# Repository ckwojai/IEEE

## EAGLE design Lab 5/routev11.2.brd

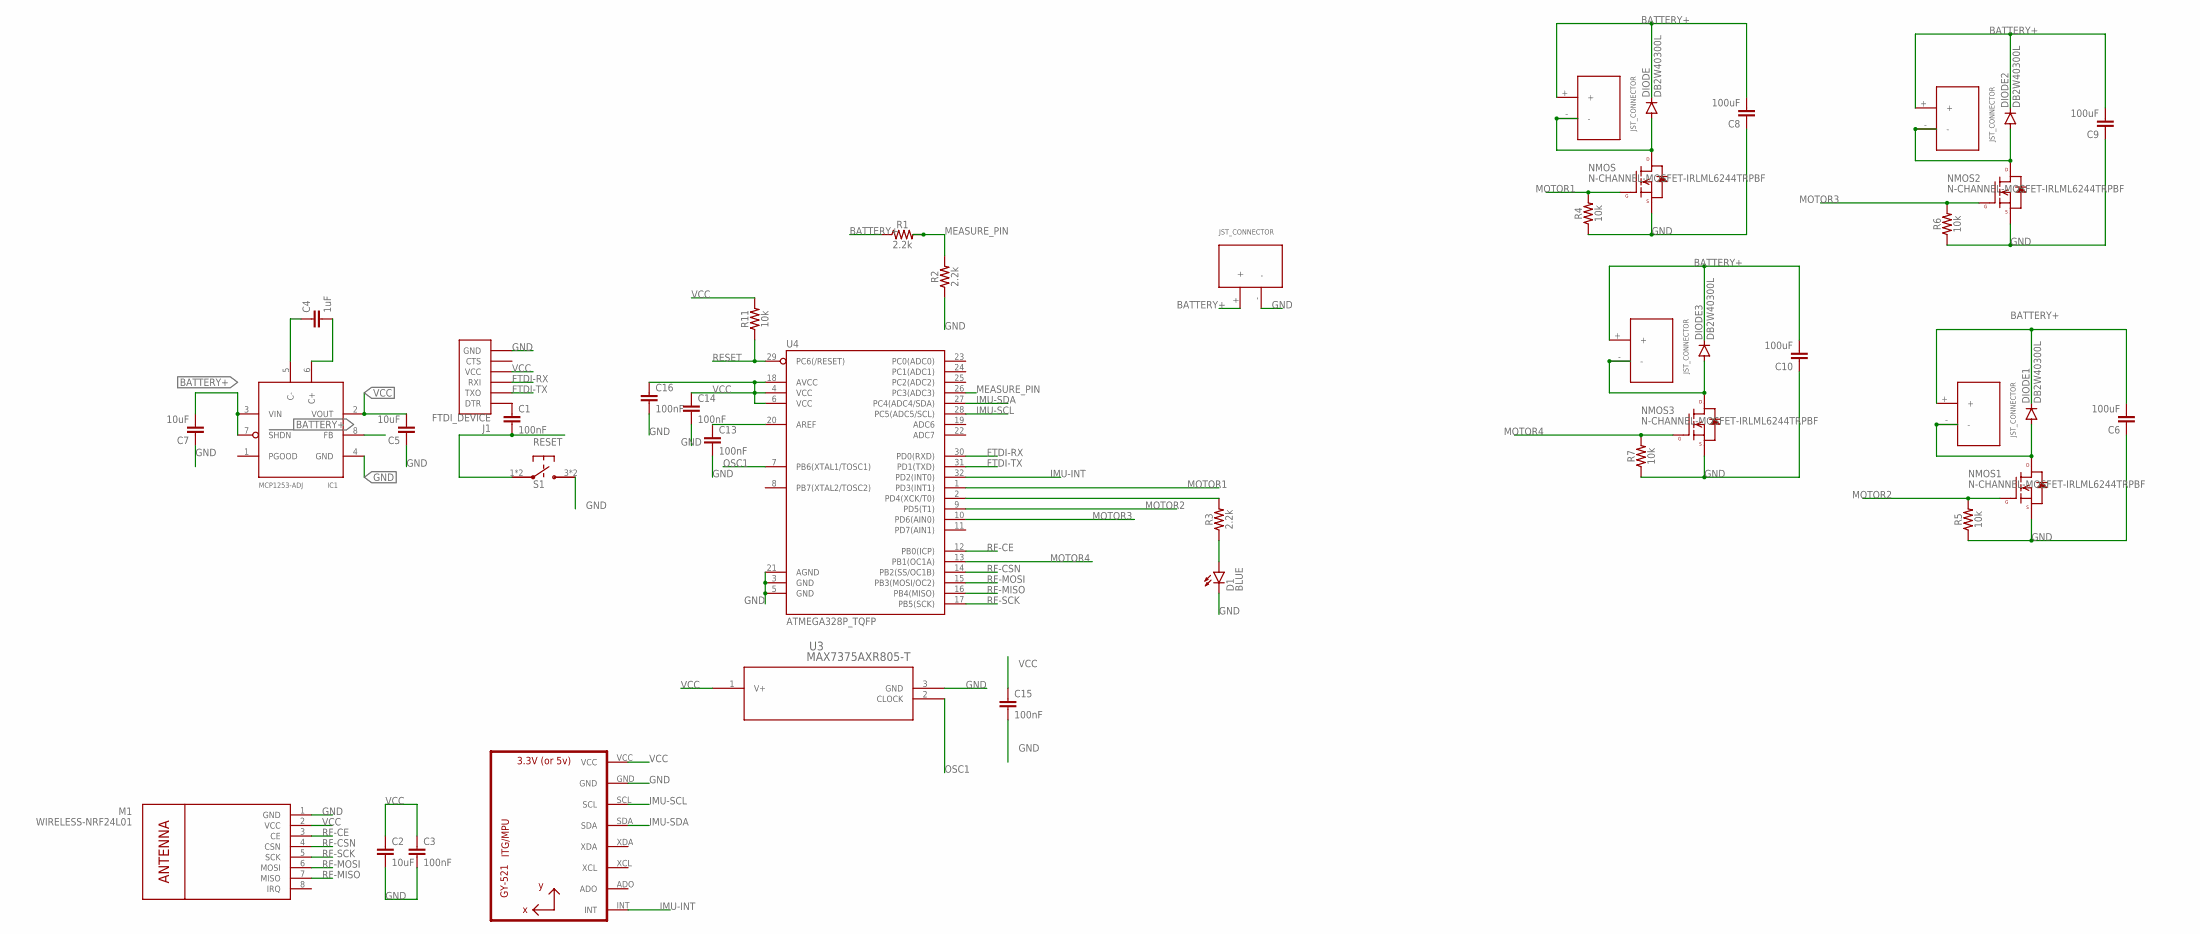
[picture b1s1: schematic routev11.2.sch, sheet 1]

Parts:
C1, C3, C13, C14, C15, C16: 100nF; 0603-CAP
C2, C5, C7: 10uF; 0603-CAP
C4: 1uF; 0603-CAP
C6, C8, C9, C10: 100uF; 1206
D1: BLUE; LED-0603
DIODE, DIODE1, DIODE2, DIODE3: DB2W40300L; MINI2-F3-B
IC1: MCP1253-ADJ; MSOP8
J1: FTDI_DEVICE; FTDI_DEVICE_SIDE
M1: WIRELESS-NRF24L01
MOTOR1, MOTOR2, MOTOR3, MOTOR4: JST_CONNECTOR_FEMALE
NMOS, NMOS1, NMOS2, NMOS3: N-CHANNEL-MOSFET-IRLML6244TRPBF; SOT23-3
R1, R2, R3: 2.2k; 0603
R4, R5, R6, R7, R11: 10k; 0603
S1: TL3315NF100Q
U2: GY-521MPU6050; GY-521
U3: MAX7375AXR805-T; 21-0075D
U4: ATMEGA328P_TQFP; TQFP32-08
U$1: JST_CONNECTOR_FEMALE

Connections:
BATTERY+: C6.2, C7.2, C8.2, C9.2, C10.2, DIODE.NEG (GPIN), DIODE1.NEG (GPIN), DIODE2.NEG (GPIN), DIODE3.NEG (GPIN), IC1.3 (VIN), IC1.7 (SHDN), IC1.8 (FB), MOTOR1.+, MOTOR2.+, MOTOR3.+, MOTOR4.+, R1.1, U$1.+
FTDI-RX: J1.P$3 (RXI), U4.30 (PD0(RXD))
FTDI-TX: J1.P$2 (TXO), U4.31 (PD1(TXD))
GND: C2.2, C3.2, C5.1, C6.1, C7.1, C8.1, C9.1, C10.1, C13.2, C14.2, C15.2, C16.2, D1.C, IC1.4 (GND), J1.P$6 (GND), M1.1 (GND), NMOS.2 (S), NMOS1.2 (S), NMOS2.2 (S), NMOS3.2 (S), R2.1, R4.1, R5.1, R6.1, R7.1, S1.3, S1.4, U2.GND, U3.3 (GND), U4.3 (GND), U4.5 (GND), U4.21 (AGND), U$1.-
IMU-INT: U2.INT, U4.32 (PD2(INT0))
IMU-SCL: U2.SCL, U4.28 (PC5(ADC5/SCL))
IMU-SDA: U2.SDA, U4.27 (PC4(ADC4/SDA))
MEASURE_PIN: R1.2, R2.2, U4.26 (PC3(ADC3))
MOTOR1: NMOS.1 (G), R4.2, U4.1 (PD3(INT1))
MOTOR2: NMOS1.1 (G), R5.2, U4.9 (PD5(T1))
MOTOR3: NMOS2.1 (G), R6.2, U4.10 (PD6(AIN0))
MOTOR4: NMOS3.1 (G), R7.2, U4.13 (PB1(OC1A))
unnamed: R3.2, U4.2 (PD4(XCK/T0))
unnamed: C1.1, J1.P$1 (DTR)
unnamed: DIODE1.POS (PPIN), MOTOR2.-, NMOS1.3 (D)
unnamed: DIODE2.POS (PPIN), MOTOR3.-, NMOS2.3 (D)
unnamed: DIODE.POS (PPIN), MOTOR1.-, NMOS.3 (D)
unnamed: DIODE3.POS (PPIN), MOTOR4.-, NMOS3.3 (D)
unnamed: C4.1, IC1.5 (C-)
unnamed: C4.2, IC1.6 (C+)
unnamed: D1.A, R3.1
unnamed: C13.1, U4.20 (AREF)
OSC1: U3.2 (CLOCK), U4.7 (PB6(XTAL1/TOSC1))
RESET: C1.2, R11.1, S1.1, S1.2, U4.29 (PC6(/RESET))
RF-CE: M1.3 (CE), U4.12 (PB0(ICP))
RF-CSN: M1.4 (CSN), U4.14 (PB2(SS/OC1B))
RF-MISO: M1.7 (MISO), U4.16 (PB4(MISO))
RF-MOSI: M1.6 (MOSI), U4.15 (PB3(MOSI/OC2))
RF-SCK: M1.5 (SCK), U4.17 (PB5(SCK))
VCC: C2.1, C3.1, C5.2, C14.1, C15.1, C16.1, IC1.2 (VOUT), J1.P$4 (VCC), M1.2 (VCC), R11.2, U2.VCC, U3.1 (V+), U4.4 (VCC), U4.6 (VCC), U4.18 (AVCC)

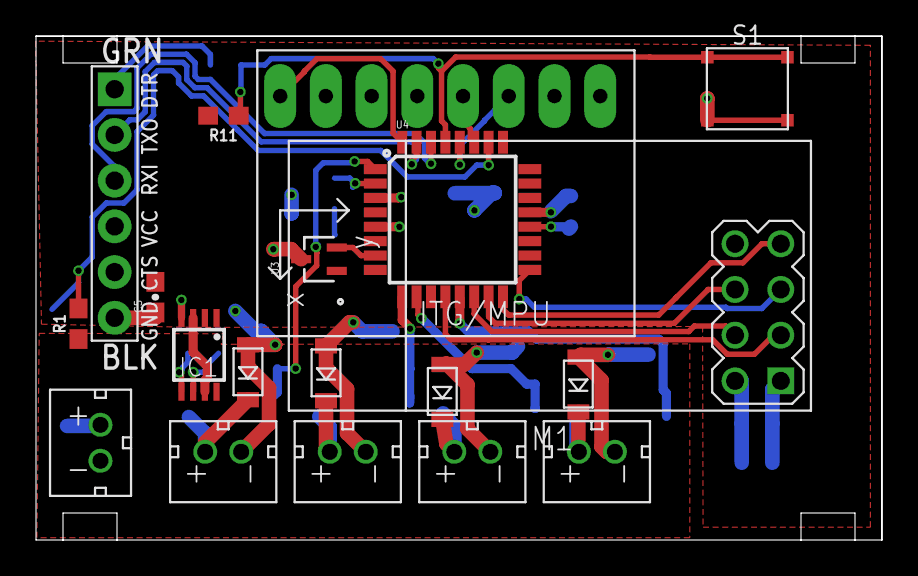
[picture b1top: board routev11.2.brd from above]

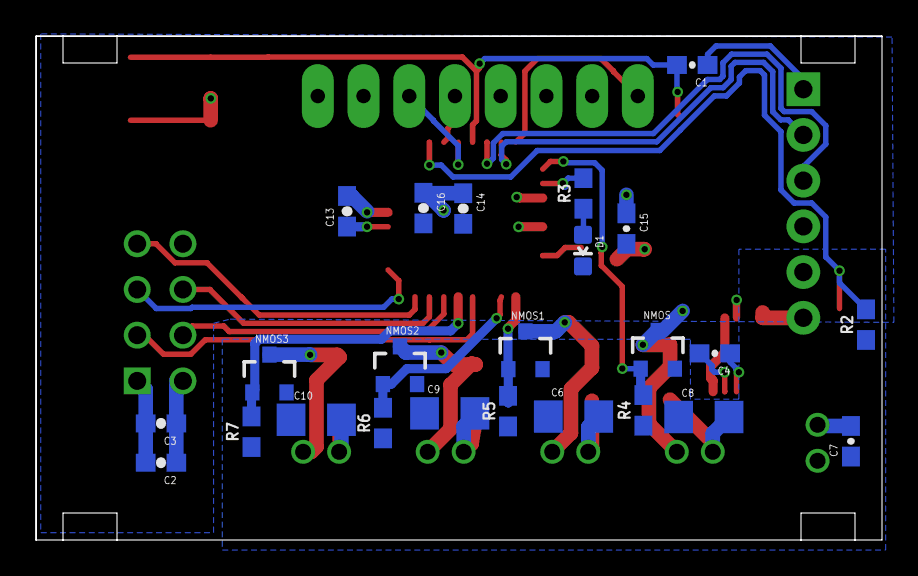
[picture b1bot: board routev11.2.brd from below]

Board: 2 copper layers, 47.0 x 28.0 mm, 43 parts (24 on the bottom side), 30 nets.

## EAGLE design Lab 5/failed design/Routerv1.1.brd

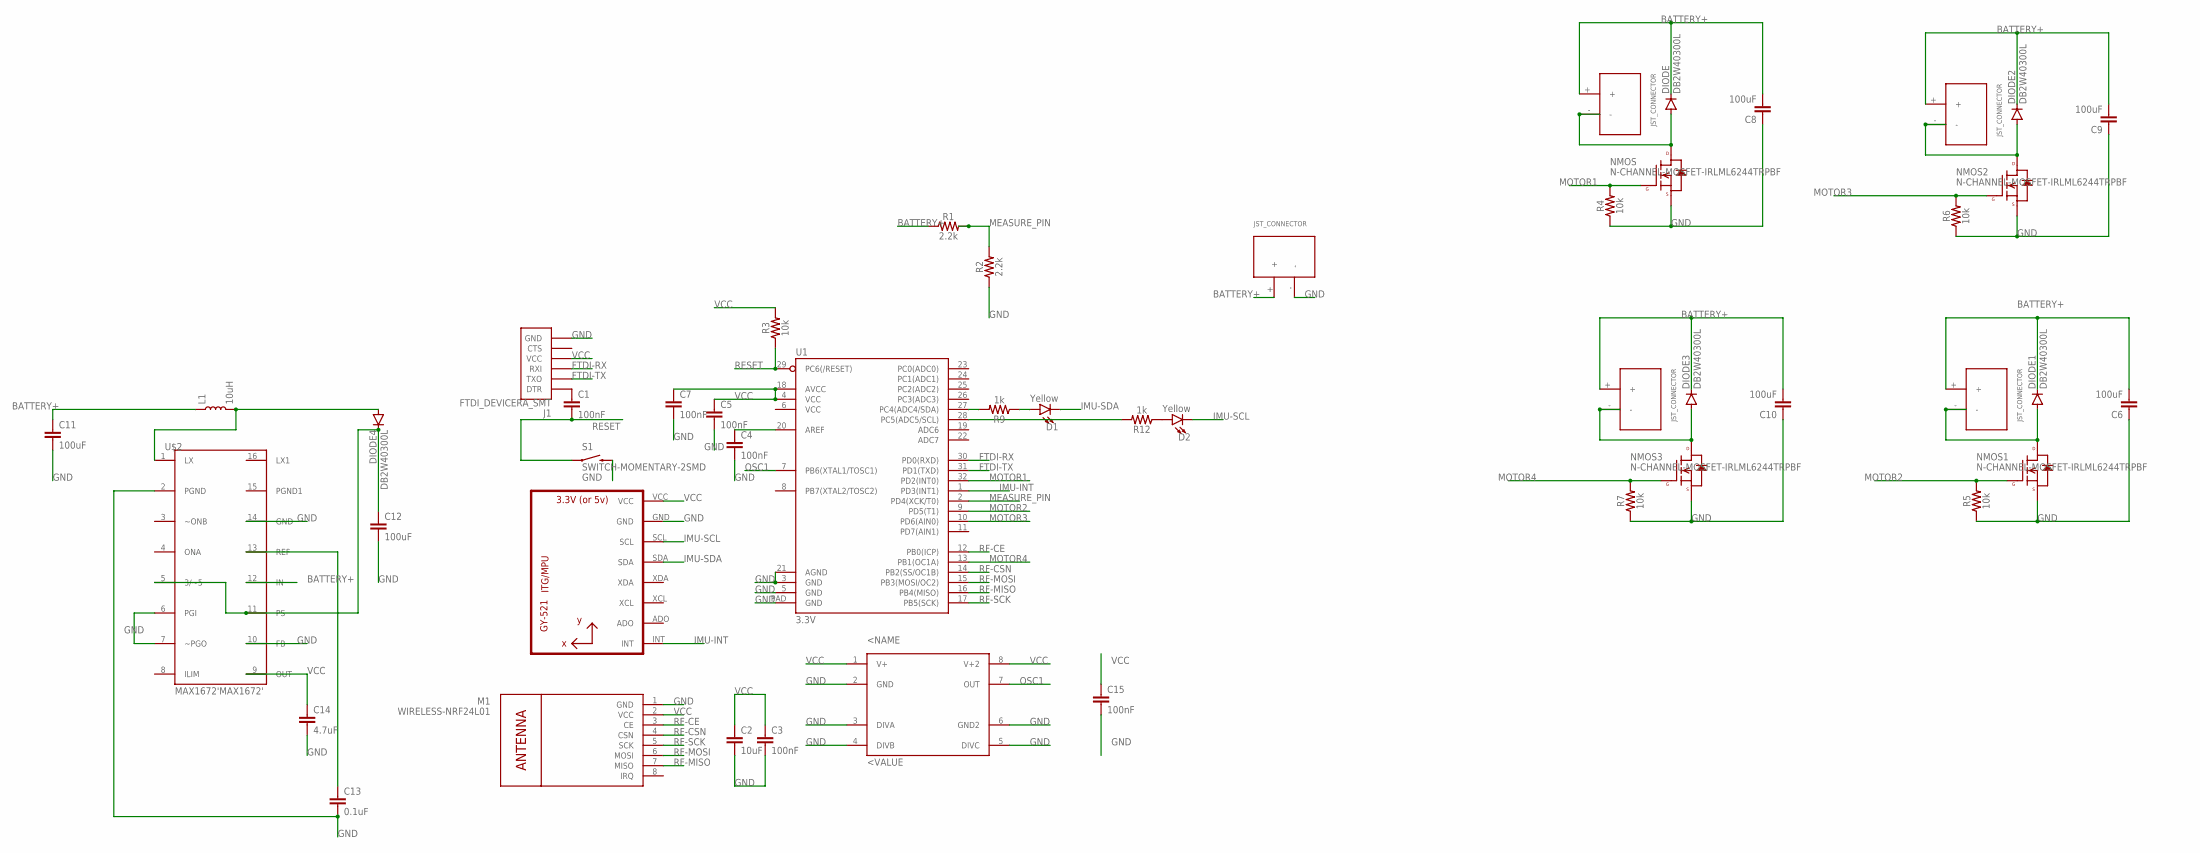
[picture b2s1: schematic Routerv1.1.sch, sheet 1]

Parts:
C1, C3, C4, C5, C7, C15: 100nF; 0603-CAP
C2: 10uF; 0603-CAP
C6, C8, C9, C10, C11, C12: 100uF; 0603-CAP
C13: 0.1uF; 0603-CAP
C14: 4.7uF; 0603-CAP
D1, D2: Yellow; LED-1206
DIODE, DIODE1, DIODE2, DIODE3, DIODE4: DB2W40300L; MINI2-F3-B
J1: FTDI_DEVICERA_SMT; FTDI_DEVICE_RA_SMT
L1: 10uH; 0603
M1: WIRELESS-NRF24L01
MOTOR, MOTOR1, MOTOR2, MOTOR3: JST_CONNECTOR_FEMALE
NMOS, NMOS1, NMOS2, NMOS3: N-CHANNEL-MOSFET-IRLML6244TRPBF; SOT23-3
R1, R2: 2.2k; 0603
R3, R4, R5, R6, R7: 10k; 0603
R9, R12: 1k; 0603
S1: SWITCH-MOMENTARY-2SMD; TACTILE-SWITCH-SMD
U1: 3.3V; MLF32-PAD
U2: GY-521MPU6050; GY-521
U$1: JST_CONNECTOR_FEMALE
U$2: MAX1672'MAX1672'; 21-0055H_16
U$3: LTC6930CMS8-8.19LTC6930CMS8-8.19; SOP65P490X110-8N

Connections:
BATTERY+: C6.2, C8.2, C9.2, C10.2, C11.1, DIODE.NEG (GPIN), DIODE1.NEG (GPIN), DIODE2.NEG (GPIN), DIODE3.NEG (GPIN), L1.1, MOTOR.+, MOTOR1.+, MOTOR2.+, MOTOR3.+, R1.1, U$1.+, U$2.12 (IN)
FTDI-RX: J1.3 (RXI), U1.30 (PD0(RXD))
FTDI-TX: J1.2 (TXO), U1.31 (PD1(TXD))
GND: C2.2, C3.2, C4.2, C5.2, C6.1, C7.2, C8.1, C9.1, C10.1, C11.2, C12.2, C13.2, C14.2, C15.2, J1.6 (GND), M1.1 (GND), NMOS.2 (S), NMOS1.2 (S), NMOS2.2 (S), NMOS3.2 (S), R2.1, R4.1, R5.1, R6.1, R7.1, S1.3 (2), U1.3 (GND), U1.5 (GND), U1.21 (AGND), U1.PAD (GND), U2.GND, U$1.-, U$2.2 (PGND), U$2.6 (PGI), U$2.7 (~PGO), U$2.10 (FB), U$2.14 (GND), U$3.2 (GND), U$3.3 (DIVA), U$3.4 (DIVB), U$3.5 (DIVC), U$3.6 (GND2)
IMU-INT: U1.1 (PD3(INT1)), U2.INT
IMU-SCL: D2.C, U2.SCL
IMU-SDA: D1.C, U2.SDA
MEASURE_PIN: R1.2, R2.2, U1.2 (PD4(XCK/T0))
MOTOR1: NMOS.1 (G), R4.2, U1.32 (PD2(INT0))
MOTOR2: NMOS1.1 (G), R5.2, U1.9 (PD5(T1))
MOTOR3: NMOS2.1 (G), R6.2, U1.10 (PD6(AIN0))
MOTOR4: NMOS3.1 (G), R7.2, U1.13 (PB1(OC1A))
unnamed: DIODE4.POS (PPIN), L1.2, U$2.1 (LX)
unnamed: C4.1, U1.20 (AREF)
unnamed: R9.2, U1.27 (PC4(ADC4/SDA))
unnamed: DIODE1.POS (PPIN), MOTOR1.-, NMOS1.3 (D)
unnamed: DIODE2.POS (PPIN), MOTOR2.-, NMOS2.3 (D)
unnamed: DIODE.POS (PPIN), MOTOR.-, NMOS.3 (D)
unnamed: DIODE3.POS (PPIN), MOTOR3.-, NMOS3.3 (D)
unnamed: D1.A, R9.1
unnamed: D2.A, R12.1
unnamed: R12.2, U1.28 (PC5(ADC5/SCL))
unnamed: C1.1, J1.1 (DTR)
OSC1: U1.7 (PB6(XTAL1/TOSC1)), U$3.7 (OUT)
RESET: C1.2, R3.1, S1.1, U1.29 (PC6(/RESET))
RF-CE: M1.3 (CE), U1.12 (PB0(ICP))
RF-CSN: M1.4 (CSN), U1.14 (PB2(SS/OC1B))
RF-MISO: M1.7 (MISO), U1.16 (PB4(MISO))
RF-MOSI: M1.6 (MOSI), U1.15 (PB3(MOSI/OC2))
RF-SCK: M1.5 (SCK), U1.17 (PB5(SCK))
VCC: C2.1, C3.1, C5.1, C7.1, C14.1, C15.1, J1.4 (VCC), M1.2 (VCC), R3.2, U1.4 (VCC), U1.18 (AVCC), U2.VCC, U$2.9 (OUT), U$3.1 (V+), U$3.8 (V+2)
VR-PS: C12.1, DIODE4.NEG (GPIN), U$2.5 (3/~5), U$2.11 (PS)
VR-REF: C13.1, U$2.13 (REF)

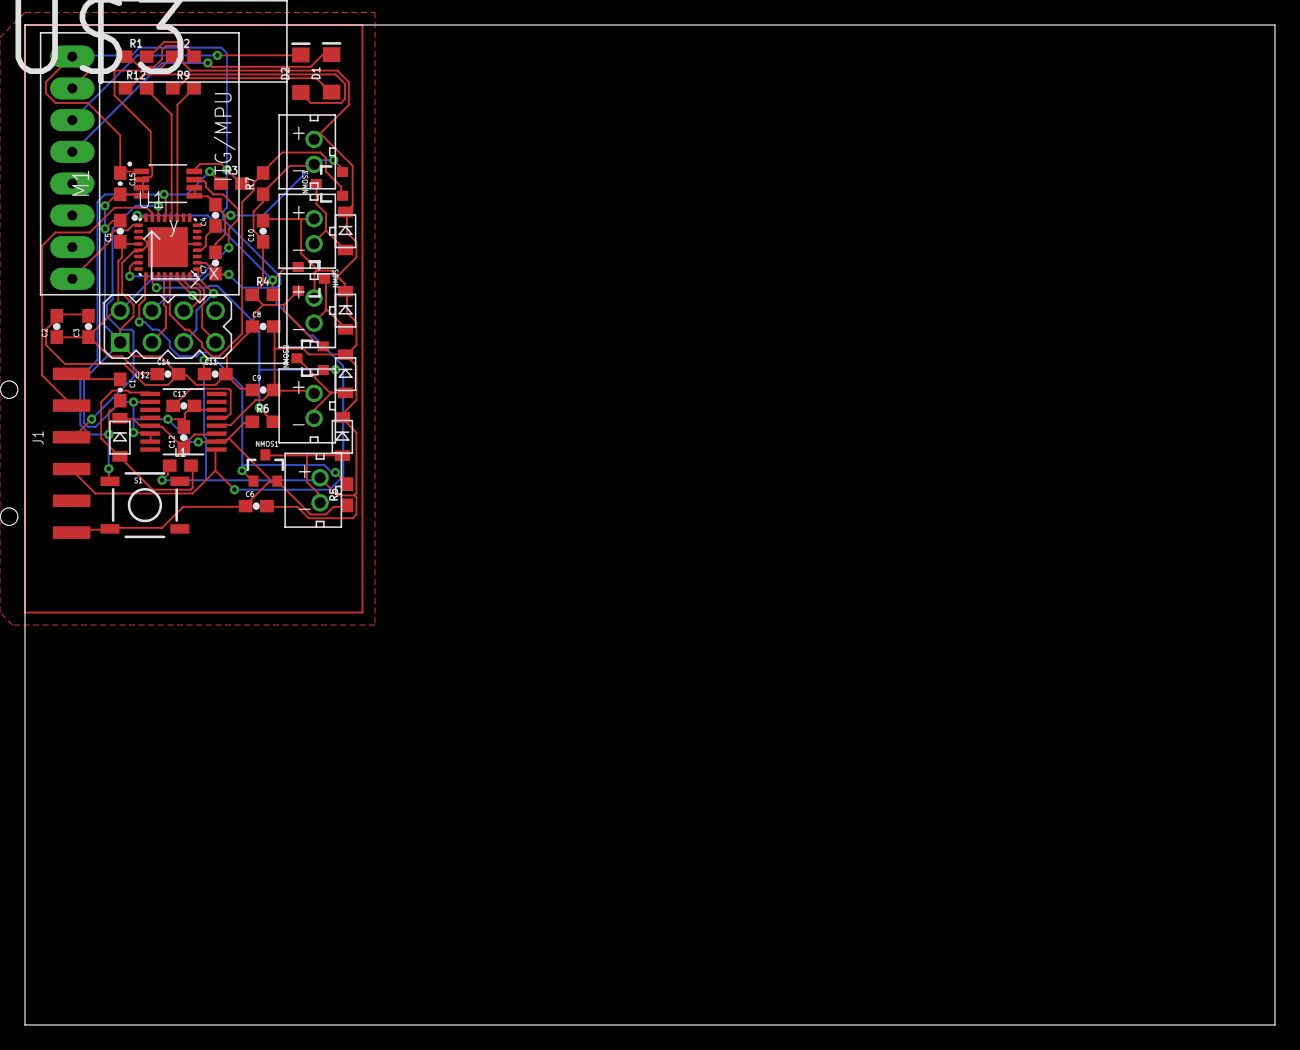
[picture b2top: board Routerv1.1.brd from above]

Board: 2 copper layers, 100.0 x 80.0 mm, 48 parts (0 on the bottom side), 33 nets.

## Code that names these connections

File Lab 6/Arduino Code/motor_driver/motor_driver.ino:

#define motor1 3
#define motor2 5
#define motor3 6
#define motor4 9
void setup() {
  // put your setup code here, to run once:
  Serial.begin(115200);
}

void loop() {
  // put your main code here, to run repeatedly:
  analogWrite(motor1, 0);
   analogWrite(motor2, 1);
    analogWrite(motor3, 2);
     analogWrite(motor4, 3);
}

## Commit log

2017-11-03 Update Arduino code
2017-11-03 game code rough draft
2017-11-03 Add Teensy code!! Working guys~~~
2017-11-04 Check out new_test.ino
2017-11-04 Working code for Arduino~ YEAAAA
2017-11-04 Update try_t
2017-11-04 Organized Arduino Code
2017-11-04 Add commentary and organize
2017-11-07 Last Update on Code; everything tested to be workin
2017-11-17 Lab 2 Initialization + Library Implementation
2017-11-17 Update .cpp implementation, this time should be right!!!
2017-11-18 Define constants in header file and create bias.ino
2017-11-18 update .cpp file
2017-11-18 Check point one done!!!
2017-11-19 Add files via upload
    updated to part D
2017-11-19 GYRO code updaet
2017-11-19 update header file
2017-11-21 updated gyro
2017-11-21 gyro - completed
2017-12-05 Create Lab 3
2017-12-05 Schematic for NMOS
2017-12-05 Lab 3
    schematic
2017-12-05 NMOS DESIGN
    schematic
2017-12-05 Variable Control Arduino Code
2017-12-05 Lab 3 initialization
2017-12-05 Organize stuffs
2017-12-05 Good Luck On FINALS everybody!!!!
2018-01-26 schematic for quad
2018-01-26 WILSON IS GONNA DESTROY AMERICA IN 2018
2018-01-26 Schematic Update
2018-01-27 Fixed needed on the google sheet
2018-01-31 90% done guys!! CHECK OUT THE NOTES.ORG file inside Lab4
2018-01-31 Migrate Bill of Materials from excel
2018-01-31 Added pull-down resistor; need VR connections
2018-01-31 voltage regulator library
2018-02-01 Need oscillator, leds
2018-02-01 Change PWM pins for motors and add oscillator
2018-02-01 Add oscillator schematic and wiring
2018-02-02 reconnected voltage regulator, added LEDs
2018-02-02 Add new oscillator and wiring!!! Good work team!!
2018-02-02 New lbr file containing all the components we've made
2018-02-02 add missing file in lbr
2018-02-02 Final Commit
2018-02-02 CHANG FTDI connection according to Thomas: RX---RX TX-TX
2018-02-04 THE MOST UDPATED VERSION OF SKETCH in LATEST_DESIGN.sch
2018-02-04 Update library: Voltage Regulator: LT1300; Oscillator: MAX7375AXR805-T
2018-02-04 MLF->TQFP, MOTOR1 now PWM, MP now analog
2018-02-04 - Voltage Regulator: SEL, SHDN to GND - MCU: LEDs to GND - Replace 10muH Inductor schematic to match BOM (0603) - Replace 100uF Capacitors schematic to match BOM (1210)
2018-02-04 Add librarys for 10uH inductor and 100uF capacitor
2018-02-04 Packages: Ind, Cap. MCU: LEDs
    100uF now 1206
    10nH now 0603
    LEDs pulled to ground
2018-02-05 Voltage regulator: SEL and SHDN to GND
2018-02-09 Lab5 init
2018-02-09 pcb arrangement
2018-02-09 layout update
2018-02-10 Created a template, things grouped together for easy placement
2018-02-10 Update template
2018-02-11 Check routev2.3.brd for one with no error
2018-02-13 Update template file, switch for the right Atmega MCU. Some advice from Arti: - Everything need to be inside the board (all white frames inside): quadcopter propellers need clearance. - Nothing under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
2018-02-15 routev4.1 idea crashed and burned: FTDI not the right module Ugggg; Update Template replacing with the correct one
2018-02-15 Latest PCB at routev7.4.brd: no DRC error!!! Hurray!!!!!!
2018-02-17 We need a redesign guys
2018-06-01 hovering code in Lab 6
2018-06-07 Update Lab6

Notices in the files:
parts and their libraries:
SparkFun-Capacitors: Licensing: Creative Commons ShareAlike 4.0 International - https://creativecommons.org/licenses/by-sa/4.0
